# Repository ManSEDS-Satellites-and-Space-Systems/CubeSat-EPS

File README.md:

# CubeSat-EPS

This is a EPS (Electric Power System) designed for 2U - 6U CubeSats.
The EPS contains 4 18650 Li-ion batteries in 2S2P configuartion.
Two power output rails are provided with 3.3v, 5v output, and 4A each.
Six MPPT (Maximum Power Point Tracking) boost converter connects the solar panels to the main bus.

## Hardware

Block diagram:

```mermaid
flowchart TD

    %% Solar Inputs
    SP1[Solar Panel 1] --> MPPT1[MPPT Boost 1]
    SP2[Solar Panel 2] --> MPPT2[MPPT Boost 2]
    SP3[Solar Panel 3] --> MPPT3[MPPT Boost 3]
    SP4[Solar Panel 4] --> MPPT4[MPPT Boost 4]
    SP5[Solar Panel 5] --> MPPT5[MPPT Boost 5]
    SP6[Solar Panel 6] --> MPPT6[MPPT Boost 6]

    MPPT1 --> BUS[Power Bus]
    MPPT2 --> BUS
    MPPT3 --> BUS
    MPPT4 --> BUS
    MPPT5 --> BUS
    MPPT6 --> BUS

    %% Battery
    BUS --> BATCTRL[Battery Charge / Protection]
    BATCTRL <--> BAT[Battery Pack]

    %% Monitoring
    BUS --> INA[INA3221 Current Monitor]
    BAT --> INA

    %% Power Rails
    BUS --> BUCK5[5V Buck Converter]
    BUS --> BUCK33[3.3V Buck Converter]

    BUCK5 --> V5[5V Rail]
    BUCK33 --> V33[3.3V Rail]

    %% MCU
    V33 --> MCU[STM32G431]
    INA --> MCU

    %% Communications
    MCU --> CAN[TCAN3414 CAN Transceiver]
    CAN --> CANBUS[CAN Bus]

    %% Watchdog
    MCU --> WDT[TPS3430 Watchdog]
    WDT -. Reset .-> MCU

    %% Loads
    V5 --> LOADS[5V Loads]
    V33 --> LOADS33[3.3V Loads]

    MCU --> H1[Heater 1 MOSFET]
    MCU --> H2[Heater 2 MOSFET]

    BAT --> H1
    BAT --> H2

    H1 --> HEATER1[Heater 1]
    H2 --> HEATER2[Heater 2]
```

Top view:

Back View:

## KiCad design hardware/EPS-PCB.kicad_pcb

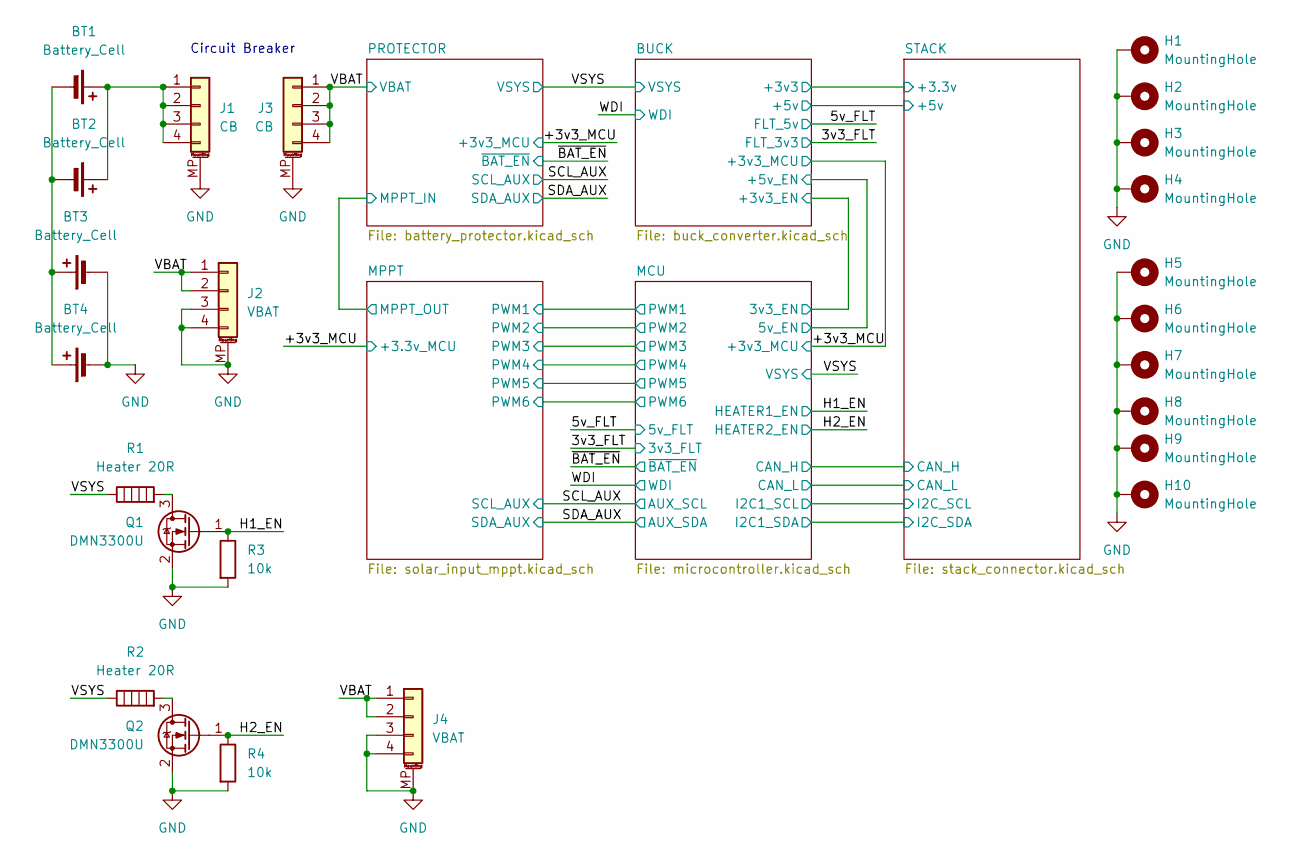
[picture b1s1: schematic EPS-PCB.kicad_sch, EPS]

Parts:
BT1, BT2, BT3, BT4: Battery_Cell; 18650-THT
H1, H2, H3, H4: MountingHole; MountingHole_3.2mm_M3_DIN965_Pad
H5, H6, H7, H8, H9, H10: MountingHole; MountingHole_2.7mm_M2.5_DIN965_Pad
J1, J3: CB; Molex_Pico-Lock_504050-0491_1x04-1MP_P1.50mm_Horizontal; Mouser Part Number 538-504050-0491
J2, J4: VBAT; Molex_Pico-Lock_504050-0491_1x04-1MP_P1.50mm_Horizontal; Mouser Part Number 538-504050-0491
Q1, Q2: DMN3300U; SOT-23; Mouser Part Number 621-DMN3300U-7
R1, R2: Heater 20R; R_Axial_DIN0617_L17.0mm_D6.0mm_P30.48mm_Horizontal; Mouser Part Number 279-4-2176793-0
R3, R4: 10k; R_0603_1608Metric; Mouser Part Number 603-AC0603DR-0710KL

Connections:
/H1_EN: Q1.1 (G), R3.1; also elsewhere on the board
/H2_EN: Q2.1 (G), R4.1; also elsewhere on the board
/VBAT: J2.1, J2.2, J3.1, J3.2, J3.3, J3.4, J4.1, J4.2; also elsewhere on the board
/VSYS: R1.1, R2.1; also elsewhere on the board
GND: BT3.2 (-), BT4.2 (-), H1.1, H2.1, H3.1, H4.1, H5.1, H6.1, H7.1, H8.1, H9.1, H10.1, J1.MP (MountPin), J2.3, J2.4, J2.MP (MountPin), J3.MP (MountPin), J4.3, J4.4, J4.MP (MountPin), Q1.2 (S), Q2.2 (S), R3.2, R4.2; also elsewhere on the board
unnamed: BT1.1 (+), BT2.1 (+), J1.1, J1.2, J1.3, J1.4
unnamed: BT1.2 (-), BT2.2 (-), BT3.1 (+), BT4.1 (+)
unnamed: Q1.3 (D), R1.2
unnamed: Q2.3 (D), R2.2

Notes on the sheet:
Circuit Breaker

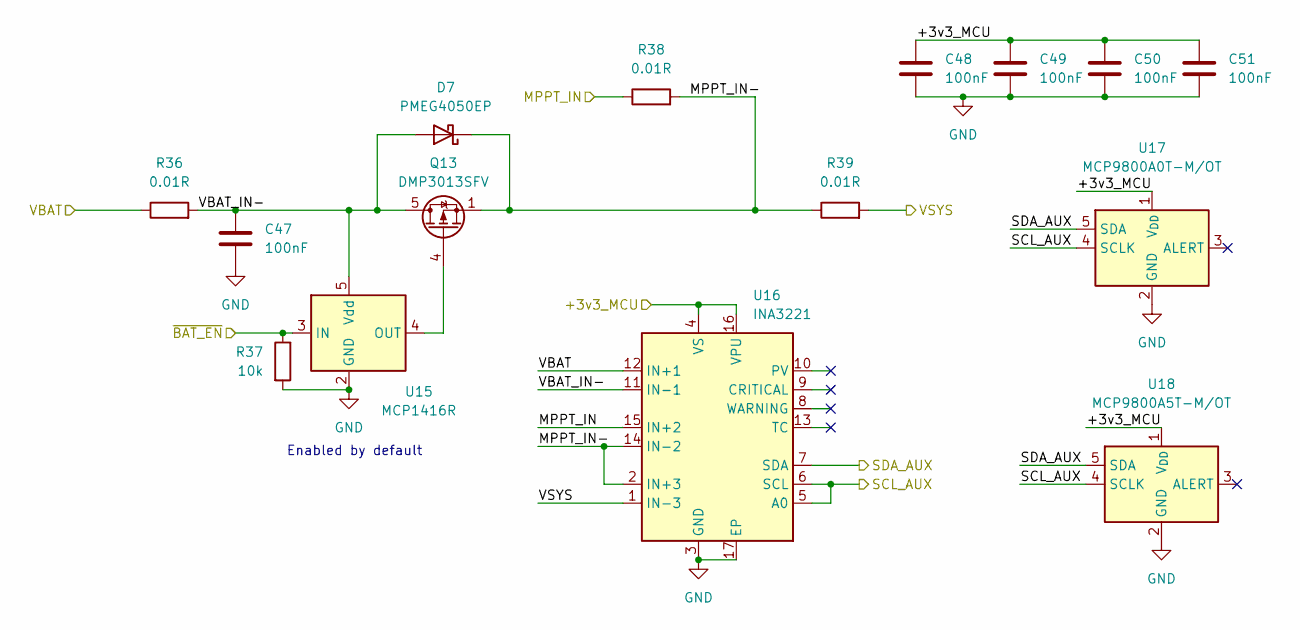
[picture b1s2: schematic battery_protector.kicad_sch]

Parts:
C47, C48, C49, C50, C51: 100nF; C_0603_1608Metric; Mouser Part Number 603-C0603JRX7R7BB104
D7: PMEG4050EP; D_SOD-128; Mouser Part Number 771-PMEG4050EP115
Q13: DMP3013SFV; Diodes_PowerDI3333-8; Mouser Part Number 621-DMP3013SFV-13
R36, R38, R39: 0.01R; R_0805_2012Metric; Mouser Part Number 603-PA0805FRF870R01L
R37: 10k; R_0603_1608Metric; Mouser Part Number 603-AC0603DR-0710KL
U15: MCP1416R; SOT-23-5; Mouser Part Number 579-MCP1416RT-E/OT
U16: INA3221; Texas_RGV0016A_VQFN-16-1EP_4x4mm_P0.65mm_EP2.1x2.1mm; Mouser Part Number 595-INA3221AIRGVR
U17: MCP9800A0T-M/OT; SOT-23-5; Mouser Part Number 579-MCP9800A0T-M/OT
U18: MCP9800A5T-M/OT; SOT-23-5; Mouser Part Number 579-MCP9800A5T-M/OT

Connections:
/+3v3_MCU: C48.1, C49.1, C50.1, C51.1, U16.4 (VS), U16.16 (VPU), U17.1 (V_{DD}), U18.1 (V_{DD}); also elsewhere on the board
/MPPT/MPPT_OUT: R38.1, U16.15 (IN+2); also elsewhere on the board
/PROTECTOR/MPPT_IN-: D7.1 (K), Q13.1 (S), Q13.2 (S), Q13.3 (S), R38.2, R39.1, U16.2 (IN+3), U16.14 (IN-2)
/PROTECTOR/VBAT_IN-: C47.1, D7.2 (A), Q13.5 (D), R36.2, U15.5 (Vdd), U16.11 (IN-1)
/SCL_AUX: U16.5 (A0), U16.6 (SCL), U17.4 (SCLK), U18.4 (SCLK); also elsewhere on the board
/SDA_AUX: U16.7 (SDA), U17.5 (SDA), U18.5 (SDA); also elsewhere on the board
/VBAT: R36.1, U16.12 (IN+1); also elsewhere on the board
/VSYS: R39.2, U16.1 (IN-3); also elsewhere on the board
/~BAT_EN: R37.1, U15.3 (IN); also elsewhere on the board
GND: C47.2, C48.2, C49.2, C50.2, C51.2, R37.2, U15.2 (GND), U16.3 (GND), U16.17 (EP), U17.2 (GND), U18.2 (GND); also elsewhere on the board
unnamed: Q13.4 (G), U15.4 (OUT)

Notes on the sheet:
Enabled by default

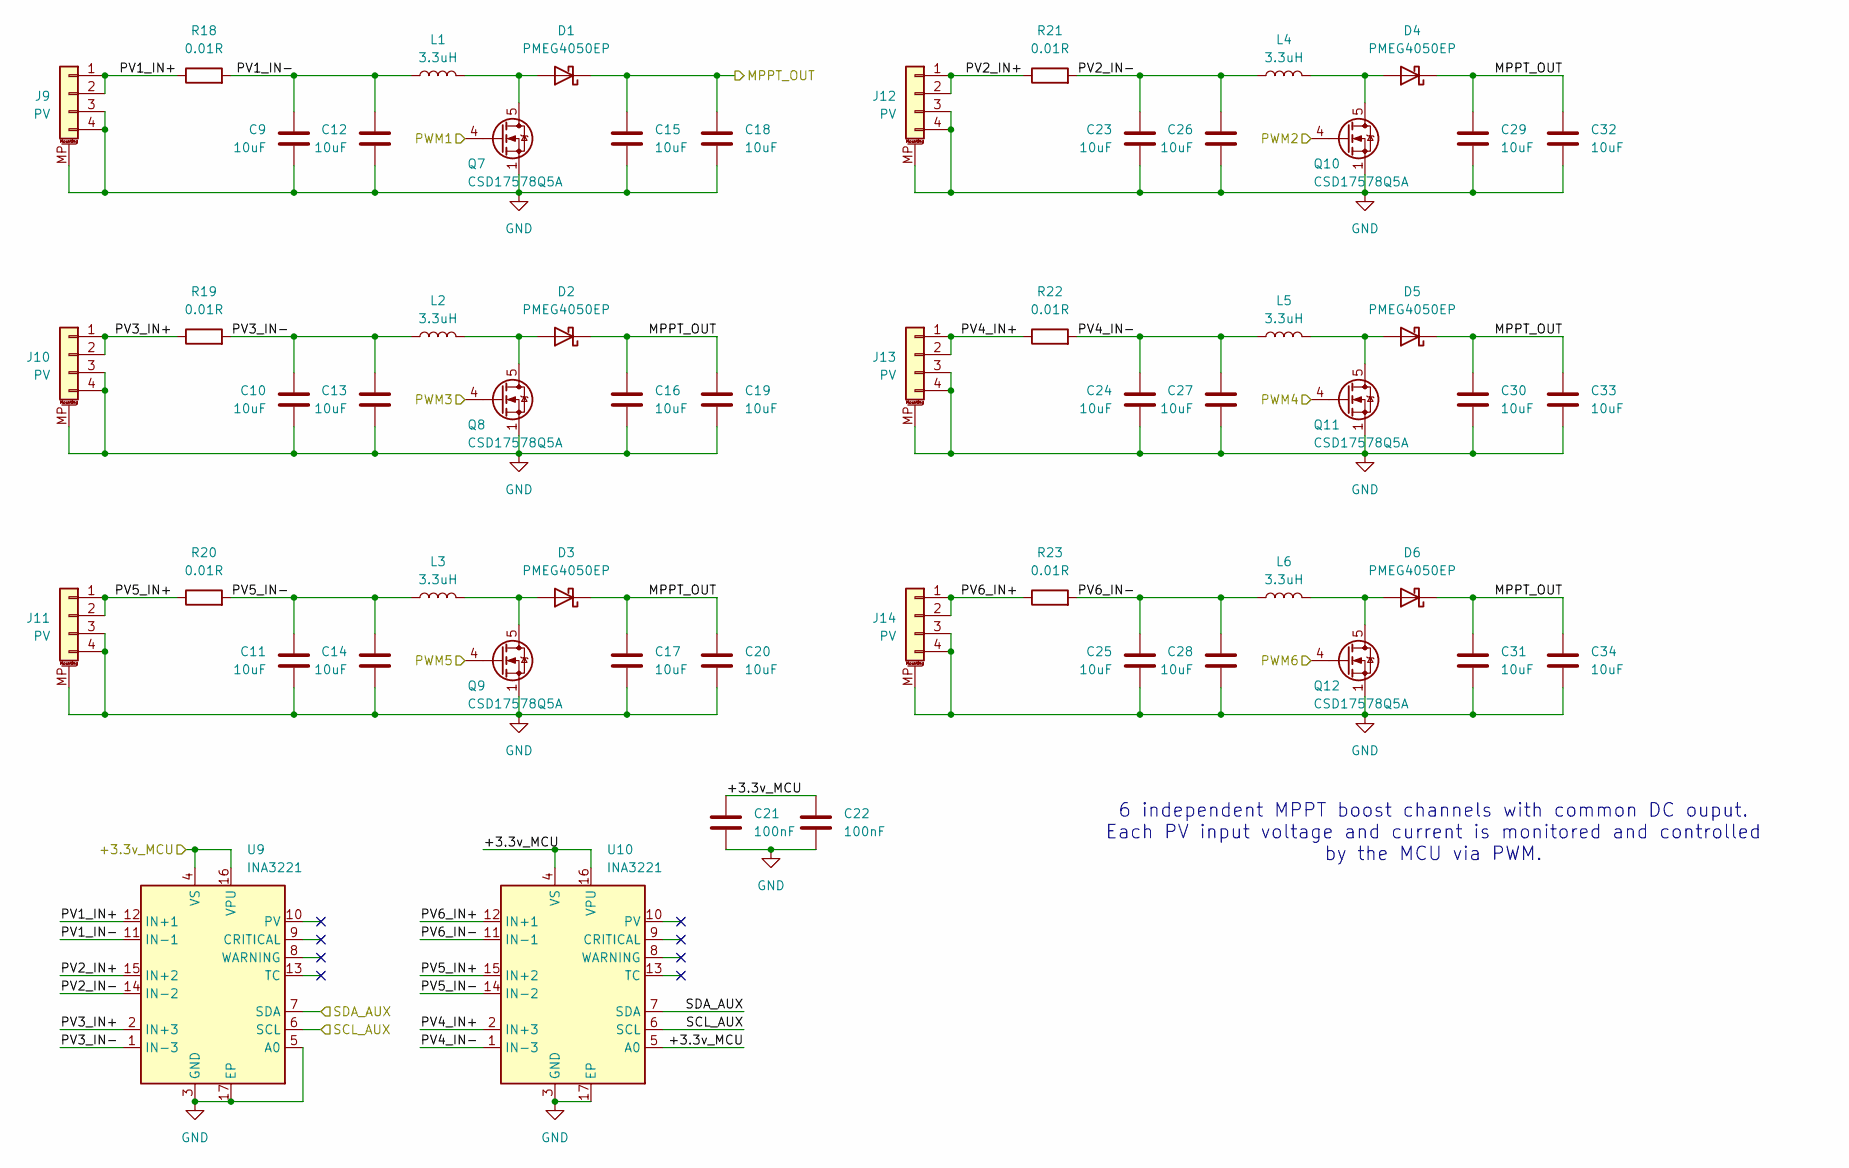
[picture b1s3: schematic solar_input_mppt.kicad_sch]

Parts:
C9, C10, C11, C12, C13, C14, C15, C16, C17, C18, C19, C20, C23, C24, C25, C26, C27, C28, C29, C30, C31, C32, C33, C34: 10uF; C_0603_1608Metric; Mouser Part Number 81-GRM188R61C106MALJ
C21, C22: 100nF; C_0603_1608Metric; Mouser Part Number 603-C0603JRX7R7BB104
D1, D2, D3, D4, D5, D6: PMEG4050EP; D_SOD-128; Mouser Part Number 771-PMEG4050EP115
J9, J10, J11, J12, J13, J14: PV; Molex_Pico-Lock_504050-0491_1x04-1MP_P1.50mm_Horizontal; Mouser Part Number 538-504050-0491
L1, L2, L3, L4, L5, L6: 3.3uH; L_Vishay_IHLP-2020; Mouser Part Number 70-IHLP2020BZER3R3M1
Q7, Q8, Q9, Q10, Q11, Q12: CSD17578Q5A; TDSON-8-1; Mouser Part Number 595-CSD17578Q5A
R18, R19, R20, R21, R22, R23: 0.01R; R_0805_2012Metric; Mouser Part Number 603-PA0805FRF870R01L
U9, U10: INA3221; Texas_RGV0016A_VQFN-16-1EP_4x4mm_P0.65mm_EP2.1x2.1mm; Mouser Part Number 595-INA3221AIRGVR

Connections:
/+3v3_MCU: C21.1, C22.1, U9.4 (VS), U9.16 (VPU), U10.4 (VS), U10.5 (A0), U10.16 (VPU); also elsewhere on the board
/MCU/PWM1: Q7.4 (G); also elsewhere on the board
/MCU/PWM2: Q10.4 (G); also elsewhere on the board
/MCU/PWM3: Q8.4 (G); also elsewhere on the board
/MCU/PWM4: Q11.4 (G); also elsewhere on the board
/MCU/PWM5: Q9.4 (G); also elsewhere on the board
/MCU/PWM6: Q12.4 (G); also elsewhere on the board
/MPPT/MPPT_OUT: C15.1, C16.1, C17.1, C18.1, C19.1, C20.1, C29.1, C30.1, C31.1, C32.1, C33.1, C34.1, D1.1 (K), D2.1 (K), D3.1 (K), D4.1 (K), D5.1 (K), D6.1 (K); also elsewhere on the board
/MPPT/PV1_IN+: J9.1, J9.2, R18.1, U9.12 (IN+1)
/MPPT/PV1_IN-: C9.1, C12.1, L1.1, R18.2, U9.11 (IN-1)
/MPPT/PV2_IN+: J12.1, J12.2, R21.1, U9.15 (IN+2)
/MPPT/PV2_IN-: C23.1, C26.1, L4.1, R21.2, U9.14 (IN-2)
/MPPT/PV3_IN+: J10.1, J10.2, R19.1, U9.2 (IN+3)
/MPPT/PV3_IN-: C10.1, C13.1, L2.1, R19.2, U9.1 (IN-3)
/MPPT/PV4_IN+: J13.1, J13.2, R22.1, U10.2 (IN+3)
/MPPT/PV4_IN-: C24.1, C27.1, L5.1, R22.2, U10.1 (IN-3)
/MPPT/PV5_IN+: J11.1, J11.2, R20.1, U10.15 (IN+2)
/MPPT/PV5_IN-: C11.1, C14.1, L3.1, R20.2, U10.14 (IN-2)
/MPPT/PV6_IN+: J14.1, J14.2, R23.1, U10.12 (IN+1)
/MPPT/PV6_IN-: C25.1, C28.1, L6.1, R23.2, U10.11 (IN-1)
/SCL_AUX: U9.6 (SCL), U10.6 (SCL); also elsewhere on the board
/SDA_AUX: U9.7 (SDA), U10.7 (SDA); also elsewhere on the board
GND: C9.2, C10.2, C11.2, C12.2, C13.2, C14.2, C15.2, C16.2, C17.2, C18.2, C19.2, C20.2, C21.2, C22.2, C23.2, C24.2, C25.2, C26.2, C27.2, C28.2, C29.2, C30.2, C31.2, C32.2, C33.2, C34.2, J9.3, J9.4, J9.MP (MountPin), J10.3, J10.4, J10.MP (MountPin), J11.3, J11.4, J11.MP (MountPin), J12.3, J12.4, J12.MP (MountPin), J13.3, J13.4, J13.MP (MountPin), J14.3, J14.4, J14.MP (MountPin), Q7.1 (S), Q7.2 (S), Q7.3 (S), Q8.1 (S), Q8.2 (S), Q8.3 (S), Q9.1 (S), Q9.2 (S), Q9.3 (S), Q10.1 (S), Q10.2 (S), Q10.3 (S), Q11.1 (S), Q11.2 (S), Q11.3 (S), Q12.1 (S), Q12.2 (S), Q12.3 (S), U9.3 (GND), U9.5 (A0), U9.17 (EP), U10.3 (GND), U10.17 (EP); also elsewhere on the board
unnamed: D1.2 (A), L1.2, Q7.5 (D)
unnamed: D2.2 (A), L2.2, Q8.5 (D)
unnamed: D3.2 (A), L3.2, Q9.5 (D)
unnamed: D4.2 (A), L4.2, Q10.5 (D)
unnamed: D5.2 (A), L5.2, Q11.5 (D)
unnamed: D6.2 (A), L6.2, Q12.5 (D)

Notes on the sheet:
6 independent MPPT boost channels with common DC ouput. Each PV input voltage and current is monitored and controlled by the MCU via PWM.

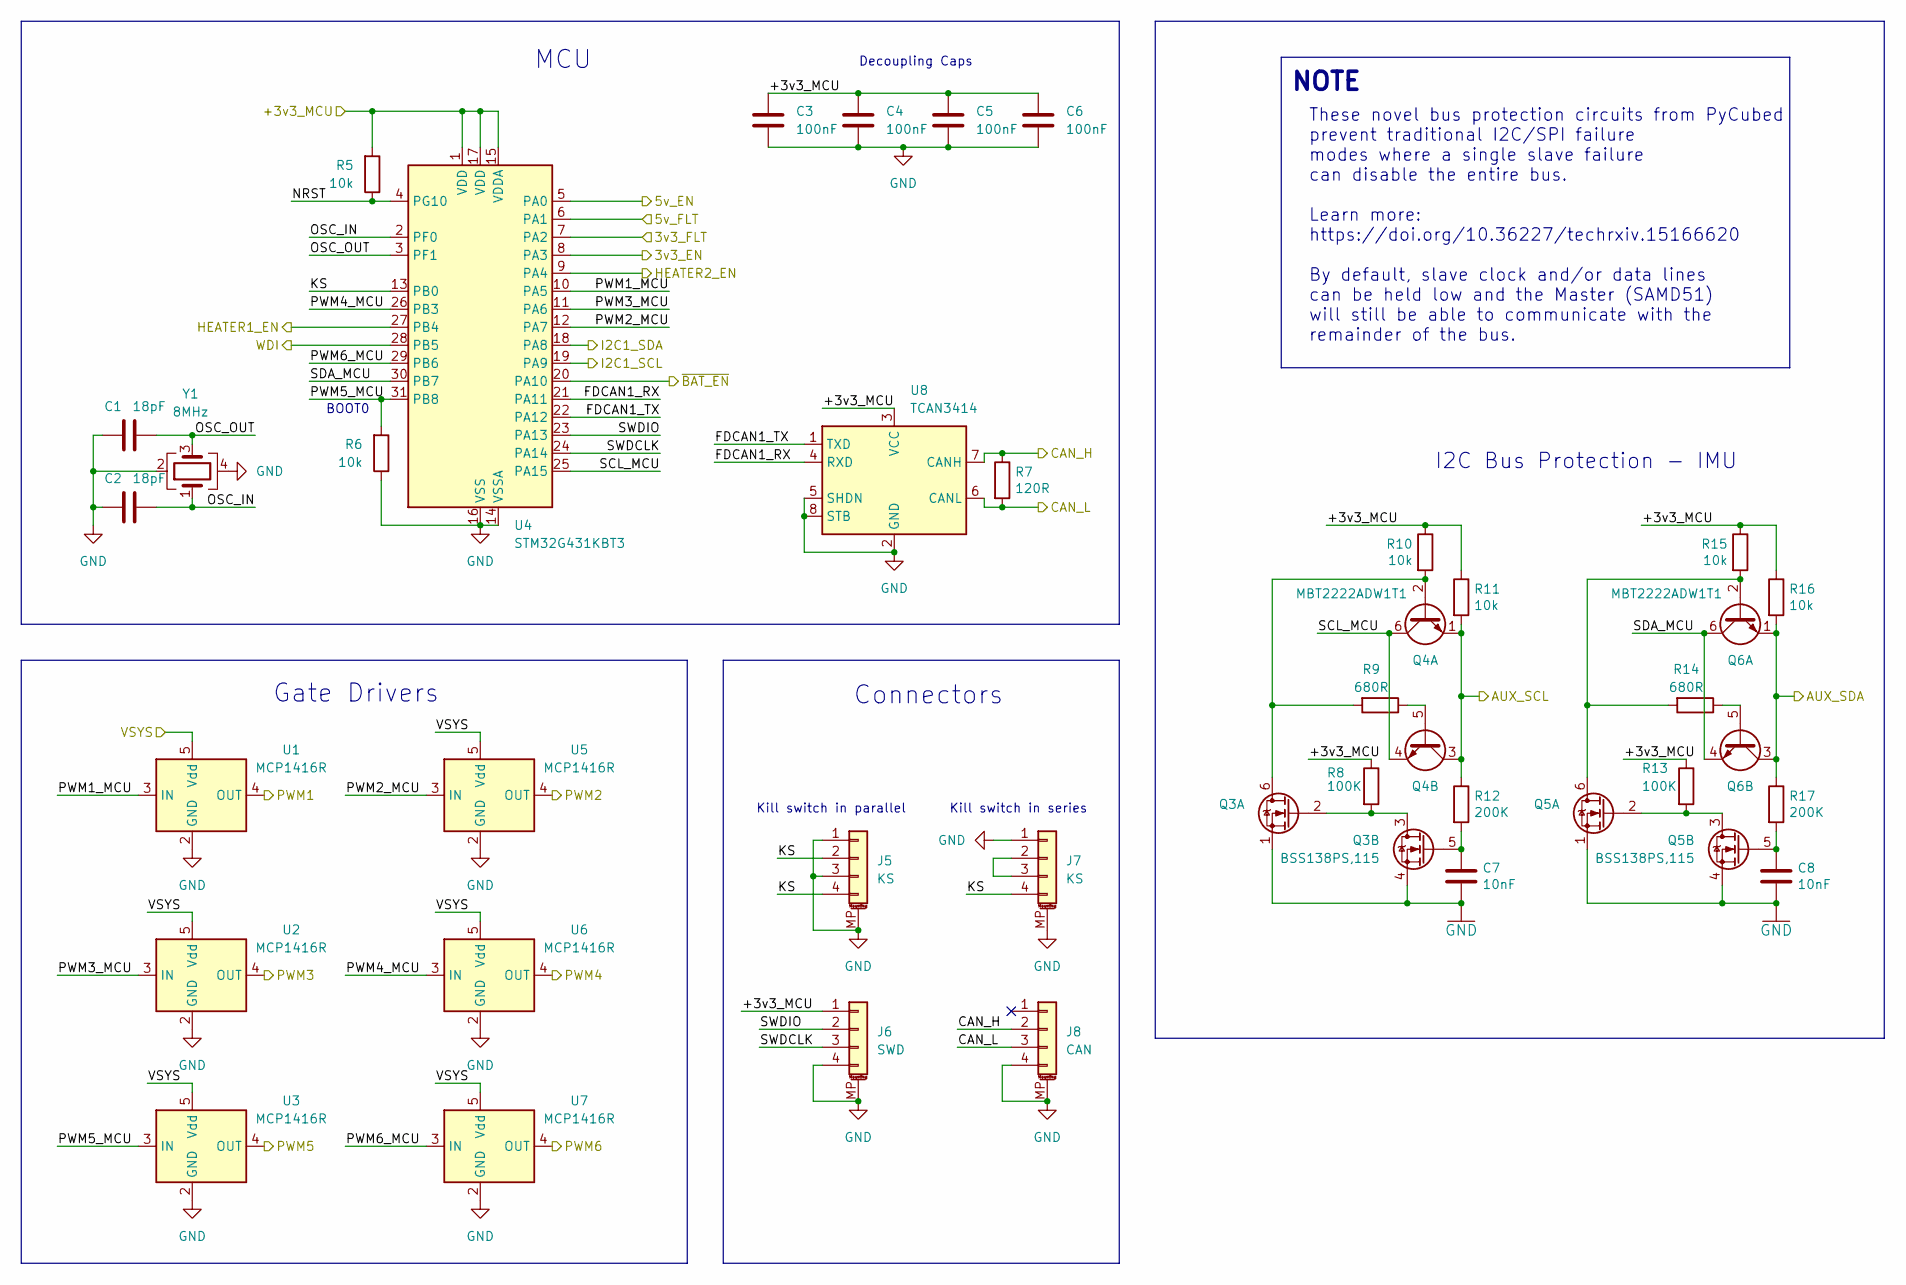
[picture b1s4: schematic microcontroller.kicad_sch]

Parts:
C1, C2: 18pF; C_0603_1608Metric; Mouser Part Number 603-CC603FRNPO9BN180
C3, C4, C5, C6: 100nF; C_0603_1608Metric; Mouser Part Number 603-C0603JRX7R7BB104
C7, C8: 10nF; C_0603_1608Metric; Mouser Part Number 603-CC0603JR7R7BB103; LCSC C1589
J5, J7: KS; Molex_Pico-Lock_504050-0491_1x04-1MP_P1.50mm_Horizontal; Mouser Part Number 538-504050-0491
J6: SWD; Molex_Pico-Lock_504050-0491_1x04-1MP_P1.50mm_Horizontal; Mouser Part Number 538-504050-0491
J8: CAN; Molex_Pico-Lock_504050-0491_1x04-1MP_P1.50mm_Horizontal; Mouser Part Number 538-504050-0491
Q3, Q5: BSS138PS,115; SOT-363_SC-70-6; Mouser Part Number 771-BSS138PS115
Q4, Q6: MBT2222ADW1T1; SOT-363_SC-70-6; Mouser Part Number 863-MBT2222ADW1T1G
R5, R6: 10k; R_0603_1608Metric; Mouser Part Number 603-AC0603DR-0710KL
R7: 120R; R_0603_1608Metric; Mouser Part Number 603-AC0603FR-07120RL; LCSC C118142
R8, R13: 100K; R_0603_1608Metric; Mouser Part Number 603-AC0603FR-7W100KL; LCSC C5369222
R9, R14: 680R; R_0603_1608Metric; Mouser Part Number 603-RT0603FRE13680RL; LCSC C112310
R10, R11, R15, R16: 10k; R_0603_1608Metric; Mouser Part Number 603-AC0603DR-0710KL; LCSC C191124
R12, R17: 200K; R_0603_1608Metric; Mouser Part Number 603-RT0603DRE07200KL; LCSC C118142
U1, U2, U3, U5, U6, U7: MCP1416R; SOT-23-5; Mouser Part Number 579-MCP1416RT-E/OT
U4: STM32G431KBT3; LQFP-32_7x7mm_P0.8mm; Mouser Part Number 511-STM32G431KBT3
U8: TCAN3414; SOIC-8_3.9x4.9mm_P1.27mm; Mouser Part Number 595-TCAN3414DRBR
Y1: 8MHz; Crystal_SMD_3225-4Pin_3.2x2.5mm; Mouser Part Number 815-M8AIG-8-1ZT

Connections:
/3v3_FLT: U4.7 (PA2); also elsewhere on the board
/5v_FLT: U4.6 (PA1); also elsewhere on the board
/+3v3_MCU: C3.1, C4.1, C5.1, C6.1, J6.1, R5.2, R8.1, R10.1, R11.1, R13.1, R15.1, R16.1, U4.1 (VDD), U4.15 (VDDA), U4.17 (VDD), U8.3 (VCC); also elsewhere on the board
/BUCK/+3v3_EN: U4.8 (PA3); also elsewhere on the board
/BUCK/+5v_EN: U4.5 (PA0); also elsewhere on the board
/H1_EN: U4.27 (PB4); also elsewhere on the board
/H2_EN: U4.9 (PA4); also elsewhere on the board
/MCU/CAN_H: J8.2, R7.1, U8.7 (CANH); also elsewhere on the board
/MCU/CAN_L: J8.3, R7.2, U8.6 (CANL); also elsewhere on the board
/MCU/FDCAN1_RX: U4.21 (PA11), U8.4 (RXD)
/MCU/FDCAN1_TX: U4.22 (PA12), U8.1 (TXD)
/MCU/I2C1_SCL: U4.19 (PA9); also elsewhere on the board
/MCU/I2C1_SDA: U4.18 (PA8); also elsewhere on the board
/MCU/KS: J5.2, J5.4, J7.4, U4.13 (PB0)
/MCU/NRST: R5.1, U4.4 (PG10)
/MCU/OSC_IN: C2.2, U4.2 (PF0), Y1.1
/MCU/OSC_OUT: C1.2, U4.3 (PF1), Y1.3
/MCU/PWM1: U1.4 (OUT); also elsewhere on the board
/MCU/PWM1_MCU: U1.3 (IN), U4.10 (PA5)
/MCU/PWM2: U5.4 (OUT); also elsewhere on the board
/MCU/PWM2_MCU: U4.12 (PA7), U5.3 (IN)
/MCU/PWM3: U2.4 (OUT); also elsewhere on the board
/MCU/PWM3_MCU: U2.3 (IN), U4.11 (PA6)
/MCU/PWM4: U6.4 (OUT); also elsewhere on the board
/MCU/PWM4_MCU: U4.26 (PB3), U6.3 (IN)
/MCU/PWM5: U3.4 (OUT); also elsewhere on the board
/MCU/PWM5_MCU: R6.2, U3.3 (IN), U4.31 (PB8)
/MCU/PWM6: U7.4 (OUT); also elsewhere on the board
/MCU/PWM6_MCU: U4.29 (PB6), U7.3 (IN)
/MCU/SCL_MCU: Q4.4 (E2), Q4.6 (C1), U4.25 (PA15)
/MCU/SDA_MCU: Q6.4 (E2), Q6.6 (C1), U4.30 (PB7)
/MCU/SWDCLK: J6.3, U4.24 (PA14)
/MCU/SWDIO: J6.2, U4.23 (PA13)
/SCL_AUX: Q4.1 (E1), Q4.3 (C2), R11.2, R12.1; also elsewhere on the board
/SDA_AUX: Q6.1 (E1), Q6.3 (C2), R16.2, R17.1; also elsewhere on the board
/VSYS: U1.5 (Vdd), U2.5 (Vdd), U3.5 (Vdd), U5.5 (Vdd), U6.5 (Vdd), U7.5 (Vdd); also elsewhere on the board
/WDI: U4.28 (PB5); also elsewhere on the board
/~BAT_EN: U4.20 (PA10); also elsewhere on the board
GND: C1.1, C2.1, C3.2, C4.2, C5.2, C6.2, C7.2, C8.2, J5.1, J5.3, J5.MP (MountPin), J6.4, J6.MP (MountPin), J7.1, J7.MP (MountPin), J8.4, J8.MP (MountPin), Q3.1 (S), Q3.4 (S), Q5.1 (S), Q5.4 (S), R6.1, U1.2 (GND), U2.2 (GND), U3.2 (GND), U4.14 (VSSA), U4.16 (VSS), U4.32 (VSS), U5.2 (GND), U6.2 (GND), U7.2 (GND), U8.2 (GND), U8.5 (SHDN), U8.8 (STB), Y1.2, Y1.4; also elsewhere on the board
unnamed: J7.2, J7.3
unnamed: Q3.6 (D), Q4.2 (B1), R9.2, R10.2
unnamed: Q3.2 (G), Q3.3 (D), R8.2
unnamed: C7.1, Q3.5 (G), R12.2
unnamed: Q4.5 (B2), R9.1
unnamed: Q5.6 (D), Q6.2 (B1), R14.2, R15.2
unnamed: Q5.2 (G), Q5.3 (D), R13.2
unnamed: C8.1, Q5.5 (G), R17.2
unnamed: Q6.5 (B2), R14.1

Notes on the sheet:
BOOT0
Kill switch in series
NOTE
I2C Bus Protection - IMU
Decoupling Caps
These novel bus protection circuits from PyCubed prevent traditional I2C/SPI failure modes where a single slave failure can disable the entire bus. Learn more: https://doi.org/10.36227/techrxiv.15166620 By default, slave clock and/or data lines can be held low and the Master (SAMD51) will still be 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
Connectors
MCU
Kill switch in parallel
Gate Drivers

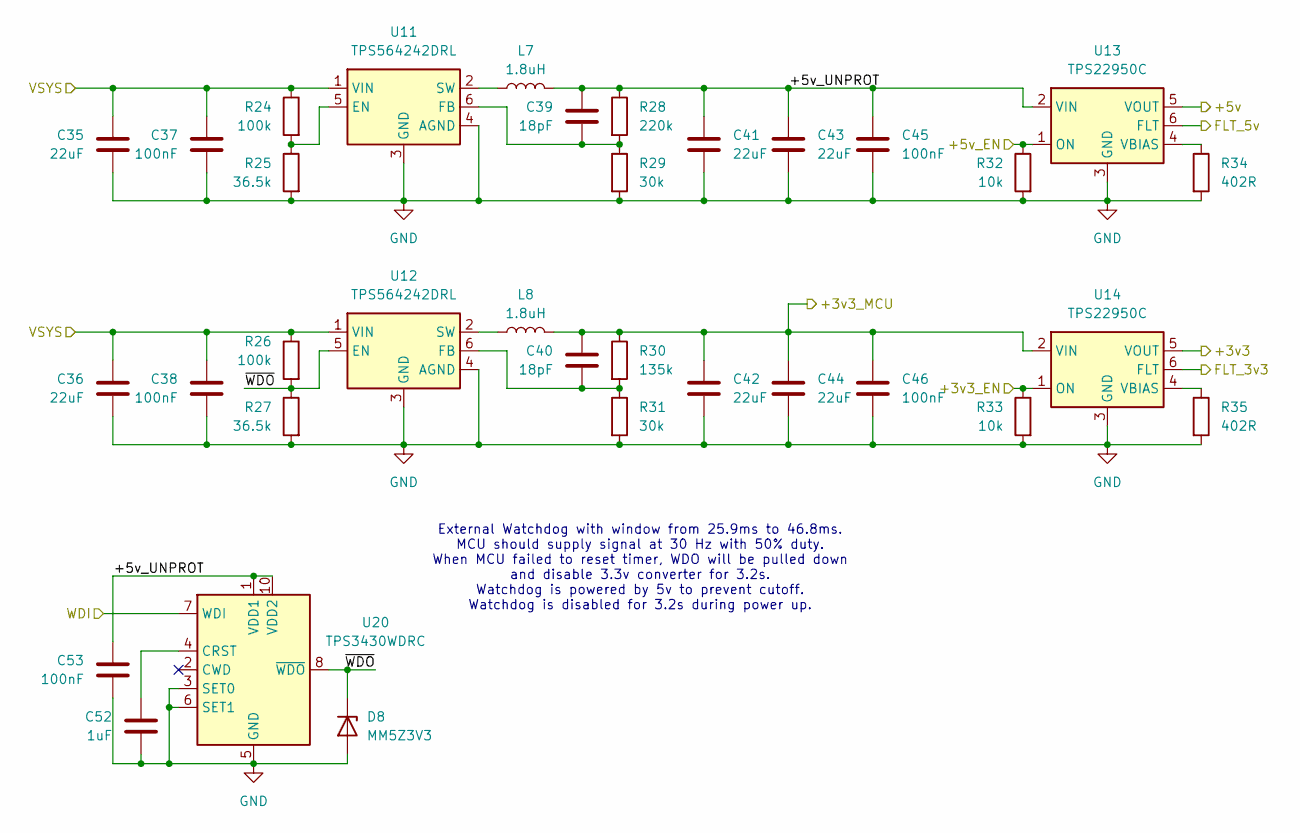
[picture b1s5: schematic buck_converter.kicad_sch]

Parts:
C35, C36, C41, C42, C43, C44: 22uF; C_0603_1608Metric; Mouser Part Number 81-ZRB18AR61C226ME1L
C37, C38, C45, C46, C53: 100nF; C_0603_1608Metric; Mouser Part Number 603-C0603JRX7R7BB104
C39, C40: 18pF; C_0603_1608Metric; Mouser Part Number 603-CC603FRNPO9BN180
C52: 1uF; C_0603_1608Metric; Mouser Part Number 603-CC603KRX5R6BB105
D8: MM5Z3V3; D_SOD-523; Mouser Part Number 637-MM5Z3V3
L7, L8: 1.8uH; L_Coilcraft_XAL6030-XXX; Mouser Part Number 994-XAL6030-182MEC
R24, R26: 100k; R_0603_1608Metric; Mouser Part Number 603-AC0603FR-7W100KL
R25, R27: 36.5k; R_0603_1608Metric; Mouser Part Number 603-RT0603DRE0736K5L
R28: 220k; R_0603_1608Metric; Mouser Part Number 603-RC0603FR-07220KL
R29, R31: 30k; R_0603_1608Metric; Mouser Part Number 603-AC0603DR-0730KL
R30: 135k; R_0603_1608Metric; Mouser Part Number 603-RT0603BRD07135KL
R32, R33: 10k; R_0603_1608Metric; Mouser Part Number 603-AC0603DR-0710KL
R34, R35: 402R; R_0603_1608Metric; Mouser Part Number 603-RT0603DRD07402RL
U11, U12: TPS564242DRL; SOT-563; Mouser Part Number 595-TPS564242DRLR
U13, U14: TPS22950C; SOT-23-6; Mouser Part Number 595-TPS22950CDDCR
U20: TPS3430WDRC; VSON-10-1EP_3x3mm_P0.5mm_EP1.65x2.4mm; Mouser Part Number 595-TPS3430WDRCR

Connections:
/3v3_FLT: U14.6 (FLT); also elsewhere on the board
/5v_FLT: U13.6 (FLT); also elsewhere on the board
/+3v3_MCU: C40.1, C42.1, C44.1, C46.1, L8.2, R30.1, U14.2 (VIN); also elsewhere on the board
/BUCK/+3v3_EN: R33.1, U14.1 (ON); also elsewhere on the board
/BUCK/+5v_EN: R32.1, U13.1 (ON); also elsewhere on the board
/BUCK/+5v_UNPROT: C39.1, C41.1, C43.1, C45.1, C53.1, L7.2, R28.1, U13.2 (VIN), U20.1 (VDD1), U20.10 (VDD2)
/BUCK/~WDO: D8.1 (K), R26.2, R27.1, U12.5 (EN), U20.8 (~WDO)
/STACK/+3.3v: U14.5 (VOUT); also elsewhere on the board
/STACK/+5v: U13.5 (VOUT); also elsewhere on the board
/VSYS: C35.1, C36.1, C37.1, C38.1, R24.1, R26.1, U11.1 (VIN), U12.1 (VIN); also elsewhere on the board
/WDI: U20.7 (WDI); also elsewhere on the board
GND: C35.2, C36.2, C37.2, C38.2, C41.2, C42.2, C43.2, C44.2, C45.2, C46.2, C52.2, C53.2, D8.2 (A), R25.2, R27.2, R29.2, R31.2, R32.2, R33.2, R34.2, R35.2, U11.3 (GND), U11.4 (AGND), U12.3 (GND), U12.4 (AGND), U13.3 (GND), U14.3 (GND), U20.3 (SET0), U20.5 (GND), U20.6 (SET1), U20.11 (GND); also elsewhere on the board
unnamed: R24.2, R25.1, U11.5 (EN)
unnamed: C39.2, R28.2, R29.1, U11.6 (FB)
unnamed: L7.1, U11.2 (SW)
unnamed: C40.2, R30.2, R31.1, U12.6 (FB)
unnamed: L8.1, U12.2 (SW)
unnamed: R34.1, U13.4 (VBIAS)
unnamed: R35.1, U14.4 (VBIAS)
unnamed: C52.1, U20.4 (CRST)

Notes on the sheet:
External Watchdog with window from 25.9ms to 46.8ms. MCU should supply signal at 30 Hz with 50% duty. When MCU failed to reset timer, WDO will be pulled down and disable 3.3v converter for 3.2s. Watchdog is powered by 5v to prevent cutoff. Watchdog is disabled for 3.2s during power up.

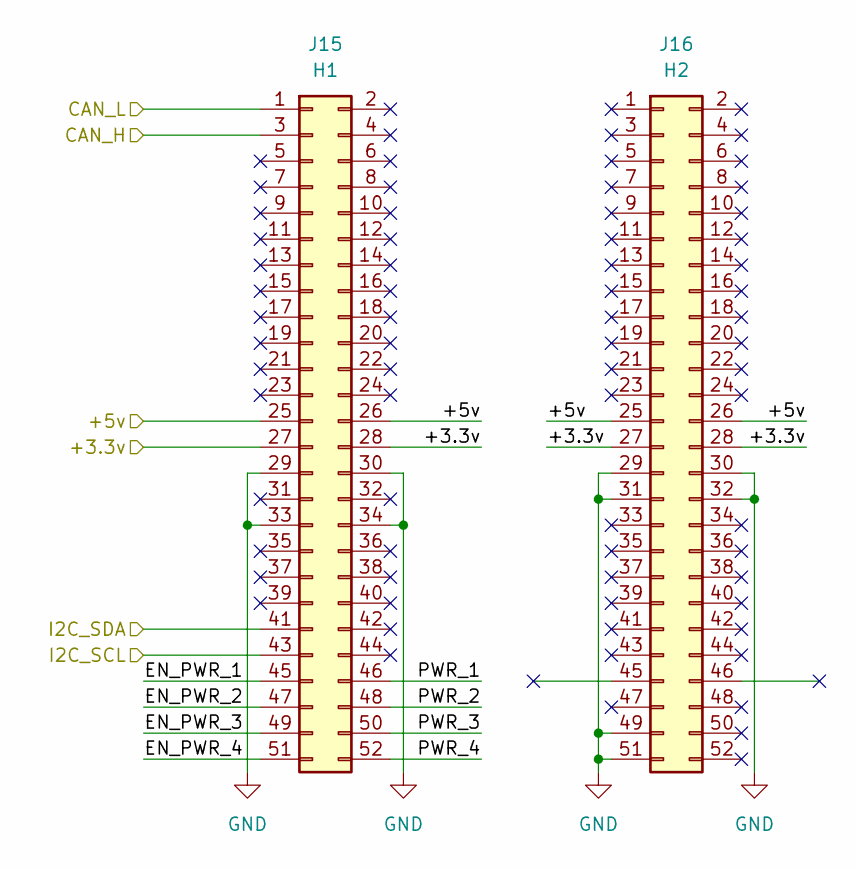
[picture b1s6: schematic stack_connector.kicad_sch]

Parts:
J15: H1; PinHeader_2x26_P2.54mm_Vertical
J16: H2; PinHeader_2x26_P2.54mm_Vertical

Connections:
/MCU/CAN_H: J15.3; also elsewhere on the board
/MCU/CAN_L: J15.1; also elsewhere on the board
/MCU/I2C1_SCL: J15.43; also elsewhere on the board
/MCU/I2C1_SDA: J15.41; also elsewhere on the board
/STACK/+3.3v: J15.27, J15.28, J16.27, J16.28; also elsewhere on the board
/STACK/+5v: J15.25, J15.26, J16.25, J16.26; also elsewhere on the board
/STACK/EN_PWR_1: J15.45
/STACK/EN_PWR_2: J15.47
/STACK/EN_PWR_3: J15.49
/STACK/EN_PWR_4: J15.51
/STACK/PWR_1: J15.46
/STACK/PWR_2: J15.48
/STACK/PWR_3: J15.50
/STACK/PWR_4: J15.52
GND: J15.29, J15.30, J15.33, J15.34, J16.29, J16.30, J16.31, J16.32, J16.49, J16.51; also elsewhere on the board

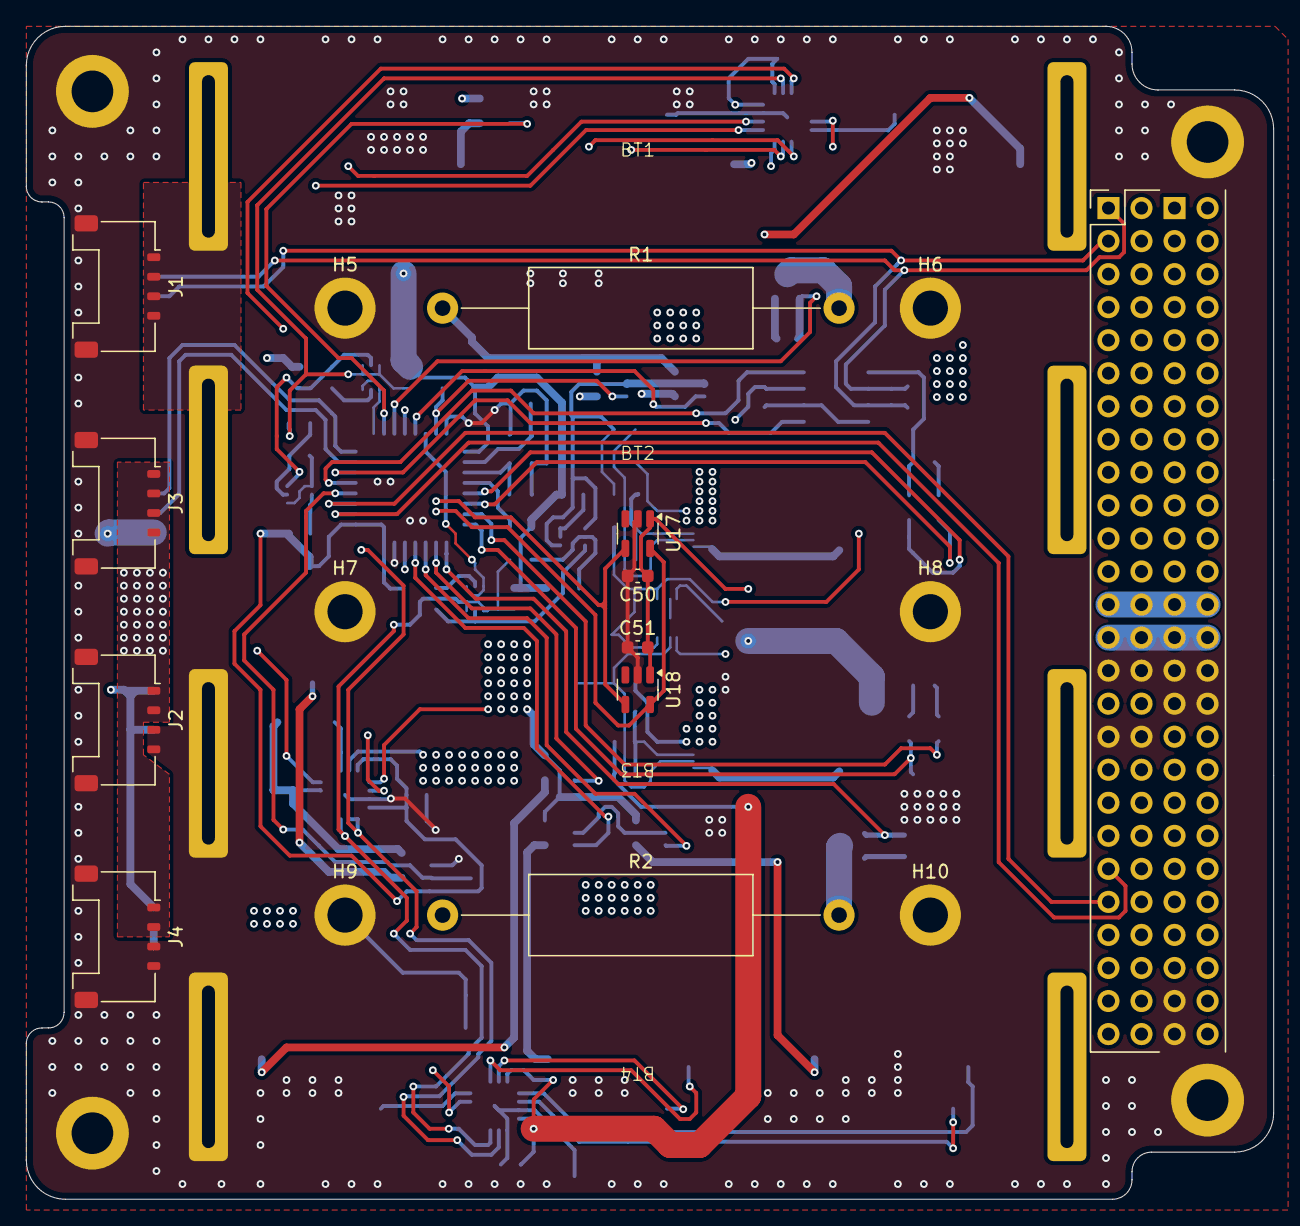
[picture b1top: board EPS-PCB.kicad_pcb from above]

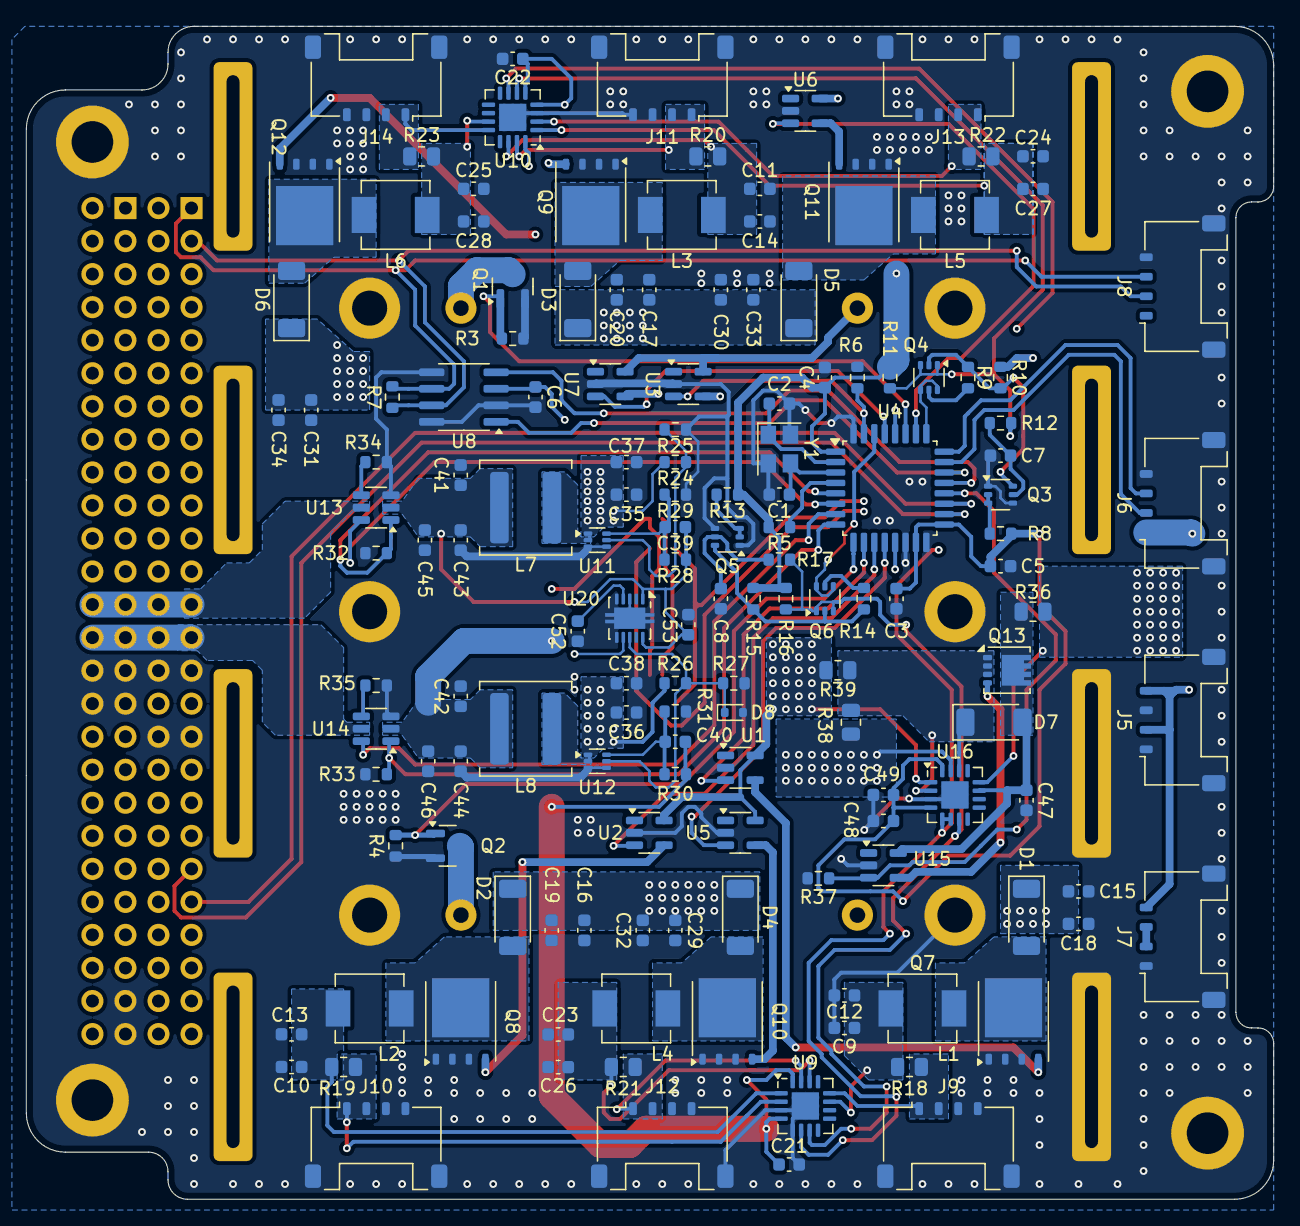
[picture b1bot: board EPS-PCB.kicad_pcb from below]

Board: 4 copper layers, 95.9 x 90.2 mm, 171 parts (145 on the bottom side), 87 nets.

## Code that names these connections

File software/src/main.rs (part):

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    let p = embassy_stm32::init(config);

    // external watchdog pin
    let extern_wdg = Output::new(p.PB5, Level::High, Speed::Medium);
    // spawn watchdog reset task
    spawner.spawn(watchdog_reset(extern_wdg).unwrap());

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    i2c_config.frequency = Hertz::khz(200);
    // init i2c master
    let i2c = I2c::new(
        p.I2C1, p.PA15, p.PB7, p.DMA1_CH1, p.DMA1_CH2, Irqs, i2c_config,
    );
    // shared I2C bus
    static I2C_BUS: StaticCell<Mutex<NoopRawMutex, I2c<'static, Async, Master>>> =
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    let i2c_dev4 = I2cDevice::new(i2c_bus);
    let i2c_dev5 = I2cDevice::new(i2c_bus);

    let pwm1_pin = PwmPin::<'_, peripherals::TIM2, timer::Ch1>::new(p.PA5, OutputType::PushPull);
    let pwm2_pin = PwmPin::<'_, peripherals::TIM3, timer::Ch2>::new(p.PA7, OutputType::PushPull);
    let pwm3_pin = PwmPin::<'_, peripherals::TIM3, timer::Ch1>::new(p.PA6, OutputType::PushPull);
    let pwm4_pin = PwmPin::<'_, peripherals::TIM2, timer::Ch2>::new(p.PB3, OutputType::PushPull);
    let pwm5_pin = PwmPin::<'_, peripherals::TIM4, timer::Ch3>::new(p.PB8, OutputType::PushPull);
    let pwm6_pin = PwmPin::<'_, peripherals::TIM4, timer::Ch1>::new(p.PB6, OutputType::PushPull);

    let timer2_chs = SimplePwm::new(
        p.TIM2,
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    let pwm5 = timer4_chs.ch3;
    let pwm6 = timer4_chs.ch1;

    let en_5v = Output::new(p.PA0, Level::Low, Speed::Medium);
    let en_3v3 = Output::new(p.PA3, Level::Low, Speed::Medium);

    let flt_5v = ExtiInput::new(p.PA1, p.EXTI1, Pull::Up, Irqs);
    let flt_3v3 = ExtiInput::new(p.PA2, p.EXTI2, Pull::Up, Irqs);

    let kill_switch = ExtiInput::new(p.PB0, p.EXTI0, Pull::Up, Irqs);

    let charge_disable = Output::new(p.PA10, Level::High, Speed::Medium);

    // spawn mppt control task
    spawner.spawn(mppt_control(i2c_dev1, i2c_dev2, pwm1, pwm2, pwm3, pwm4, pwm5, pwm6, charge_disable).unwrap());
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    spawner.spawn(eps_control(en_5v, en_3v3, flt_5v, flt_3v3, kill_switch).unwrap());

    // initialise can
    let mut can_config = CanConfigurator::new(p.FDCAN1, p.PA11, p.PA12, Irqs);
    // set bitrate
    can_config.set_bitrate(500_000);

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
